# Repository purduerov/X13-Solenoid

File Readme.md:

# Readme for X13-Solenoid

Whenever you make a new part, download the datasheet and save it here _**and**_ with the part in the parts library

Always pull other people's changes before beginning to work
`git pull`

Be sure to push your changes after  working on them. Run:
1. `git add .` to add any files in this directory or a subdirectory
or `git add -u` to add any modified files
2. (Optional) `git clean -nX` to see what ignored files can be removed
	`git clean -fX` removes ignored files (Eagle backups)
3. `git commit -m "helpful commit message"` with a description of the work that you did
4. `git push` to push your work to github

Other helpful commands
* `git status` says information about modified and staged files
* `git log` shows the recent commits of the repository
* `git log filename.extension` show the recent commits for just that file
* `git checkout first-couple-letter-of-commit-id` lets you go back to a previous version
* `git checkout master` brings you back to the latest commit
* `git tag` lists the tags
* `git tag -a orderX -m "the version of the board placed for the X'th order"` tag a specific commit
* `git push --tags` needed to push tags to remote
* `git show orderX` show the commit log for the given tag
* `git checkout orderX` go back and interact with the files at the tagged commit

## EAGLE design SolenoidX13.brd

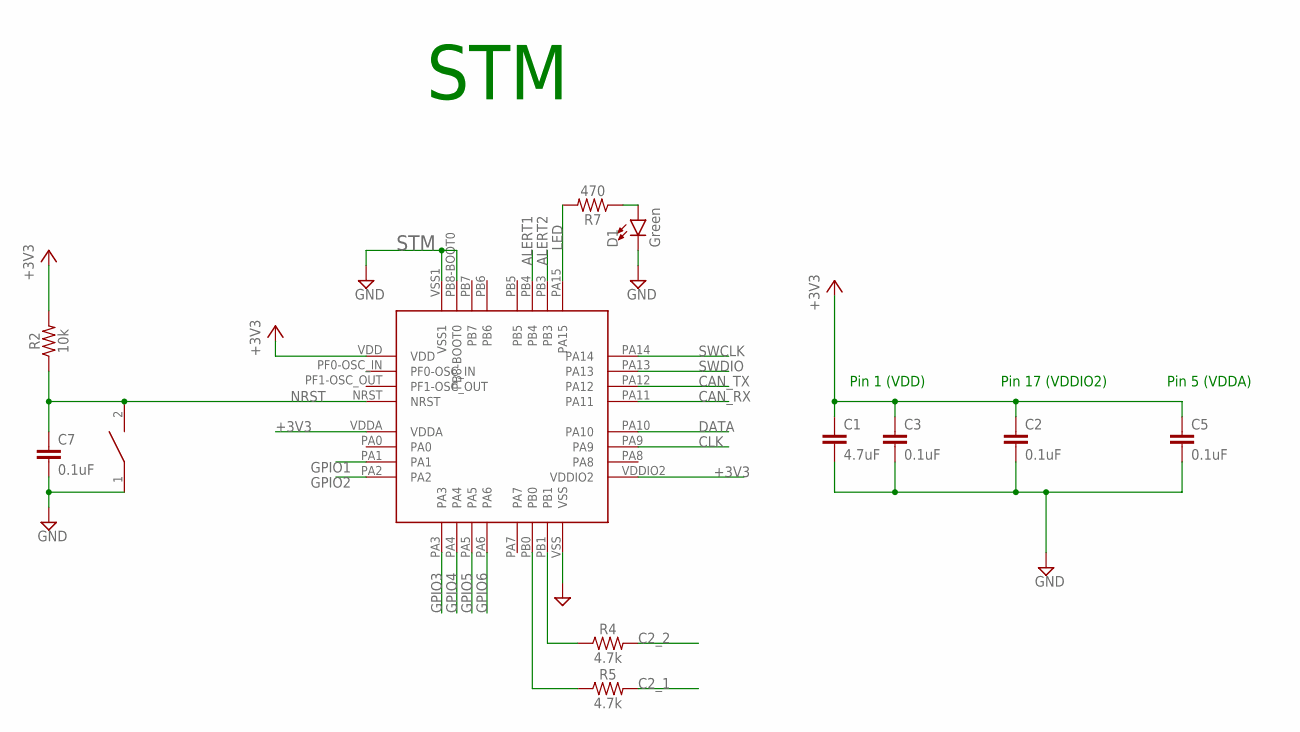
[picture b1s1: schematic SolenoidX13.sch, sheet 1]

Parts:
C1: 4.7uF; 0603
C2, C3, C5, C7: 0.1uF; 0603
D1: Green; LED-0603
R2: 10k; 0603
R4, R5: 4.7k; 0603
R7: 470; 0603
RESET: DISCRETECOMPONENTS_SWITCH; DISCRETECOMPONENTS_SW_2512
STM: STM32F042K6T6

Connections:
+3V3: C1.1, C2.1, C3.1, C5.1, R2.2, STM.VDD, STM.VDDA, STM.VDDIO2; also elsewhere on the board
ALERT1: STM.PB4; also elsewhere on the board
ALERT2: STM.PB3; also elsewhere on the board
C2_1: R5.2; also elsewhere on the board
C2_2: R4.2; also elsewhere on the board
CAN_RX: STM.PA11; also elsewhere on the board
CAN_TX: STM.PA12; also elsewhere on the board
CLK: STM.PA9; also elsewhere on the board
DATA: STM.PA10; also elsewhere on the board
GND: C1.2, C2.2, C3.2, C5.2, C7.2, D1.C, RESET.1, STM.PB8-BOOT0, STM.VSS, STM.VSS1; also elsewhere on the board
GPIO1: STM.PA1; also elsewhere on the board
GPIO2: STM.PA2; also elsewhere on the board
GPIO3: STM.PA3; also elsewhere on the board
GPIO4: STM.PA4; also elsewhere on the board
GPIO5: STM.PA5; also elsewhere on the board
GPIO6: STM.PA6; also elsewhere on the board
LED: R7.2, STM.PA15
unnamed: R4.1, STM.PB1
unnamed: R5.1, STM.PB0
unnamed: D1.A, R7.1
NRST: C7.1, R2.1, RESET.2, STM.NRST; also elsewhere on the board
SWCLK: STM.PA14; also elsewhere on the board
SWDIO: STM.PA13; also elsewhere on the board

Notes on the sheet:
Pin 1 (VDD)
Pin 17 (VDDIO2)
Pin 5 (VDDA)
STM

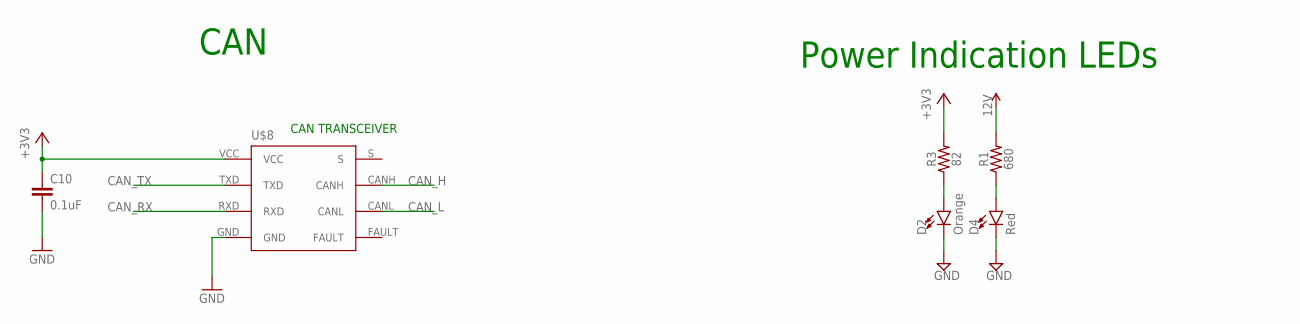
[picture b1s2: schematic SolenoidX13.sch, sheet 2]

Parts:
C10: 0.1uF; 0603
D2: Orange; LED-0603
D4: Red; LED-0603
R1: 680; 0603
R3: 82; 0603
U$8: TCAN337D

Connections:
12V: R1.2; also elsewhere on the board
+3V3: C10.1, R3.2, U$8.VCC; also elsewhere on the board
CAN_H: U$8.CANH; also elsewhere on the board
CAN_L: U$8.CANL; also elsewhere on the board
CAN_RX: U$8.RXD; also elsewhere on the board
CAN_TX: U$8.TXD; also elsewhere on the board
GND: C10.2, D2.C, D4.C, U$8.GND; also elsewhere on the board
unnamed: D4.A, R1.1
unnamed: D2.A, R3.1

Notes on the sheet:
Power Indication LEDs
CAN
CAN TRANSCEIVER

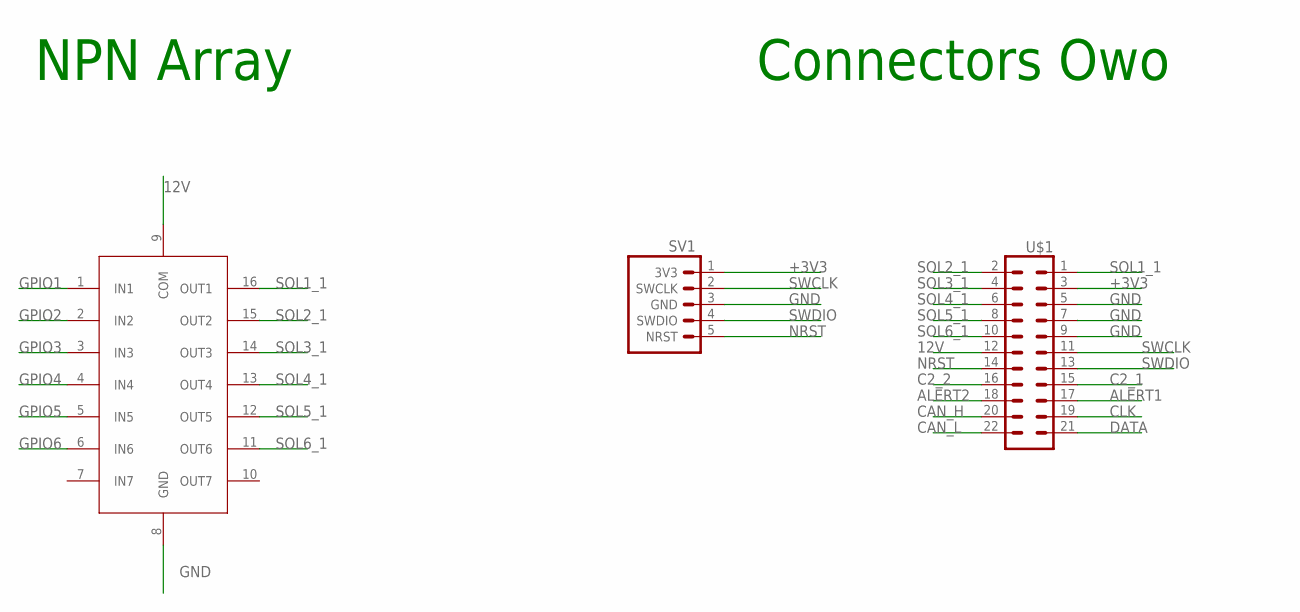
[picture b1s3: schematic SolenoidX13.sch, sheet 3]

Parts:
SV1: 3V3 -SWCLK-GND-SWDIO- NRST; 1X05
U1: ULN2003V12
U$1: SOL-TO-BKP; MMS-111-01-DV

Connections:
12V: U1.9 (COM), U$1.12; also elsewhere on the board
+3V3: SV1.1 (3V3), U$1.3; also elsewhere on the board
ALERT1: U$1.17; also elsewhere on the board
ALERT2: U$1.18; also elsewhere on the board
C2_1: U$1.15; also elsewhere on the board
C2_2: U$1.16; also elsewhere on the board
CAN_H: U$1.20; also elsewhere on the board
CAN_L: U$1.22; also elsewhere on the board
CLK: U$1.19; also elsewhere on the board
DATA: U$1.21; also elsewhere on the board
GND: SV1.3 (GND), U1.8 (GND), U$1.5, U$1.7, U$1.9; also elsewhere on the board
GPIO1: U1.1 (IN1); also elsewhere on the board
GPIO2: U1.2 (IN2); also elsewhere on the board
GPIO3: U1.3 (IN3); also elsewhere on the board
GPIO4: U1.4 (IN4); also elsewhere on the board
GPIO5: U1.5 (IN5); also elsewhere on the board
GPIO6: U1.6 (IN6); also elsewhere on the board
NRST: SV1.5 (NRST), U$1.14; also elsewhere on the board
SOL1_1: U1.16 (OUT1), U$1.1
SOL2_1: U1.15 (OUT2), U$1.2
SOL3_1: U1.14 (OUT3), U$1.4
SOL4_1: U1.13 (OUT4), U$1.6
SOL5_1: U1.12 (OUT5), U$1.8
SOL6_1: U1.11 (OUT6), U$1.10
SWCLK: SV1.2 (SWCLK), U$1.11; also elsewhere on the board
SWDIO: SV1.4 (SWDIO), U$1.13; also elsewhere on the board

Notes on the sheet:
NPN Array
Connectors Owo

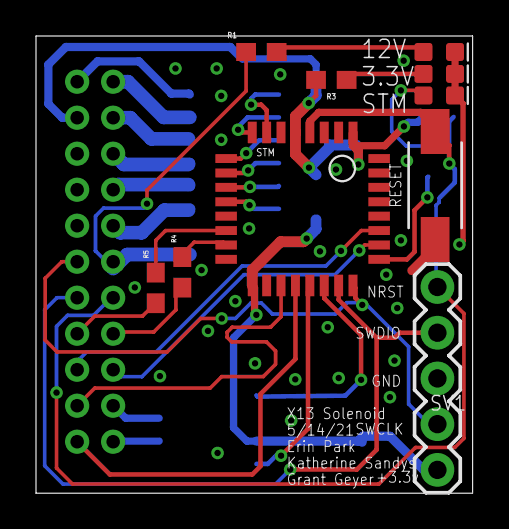
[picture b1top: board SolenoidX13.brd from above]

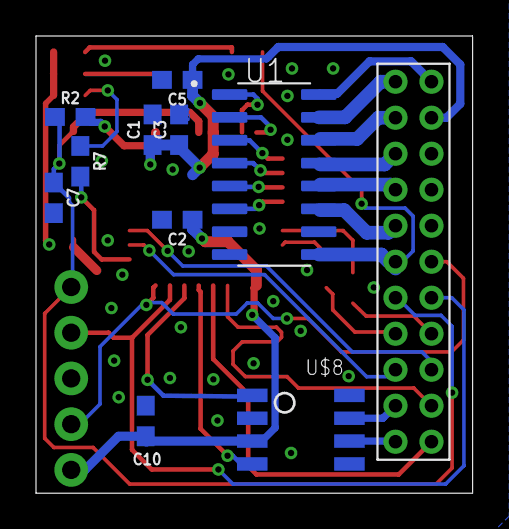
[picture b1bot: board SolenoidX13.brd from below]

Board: 2 copper layers, 24.3 x 25.4 mm, 21 parts (10 on the bottom side), 34 nets.

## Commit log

2020-11-12 First commit with setup
2020-12-03 owo?
2020-12-03 board is done lol
2020-12-03 it is smol now, cap gulag is gone, reset switch updated, clt part added to parts lib
2020-12-04 ready for design review tbh
2020-12-05 okie
2020-12-06 final
2021-01-01 Pretty much ready for production (owo)
2021-01-05 Added nrst pin to connector and routed
2021-01-05 smol changes
2021-01-07 added an OWO
2021-01-09 ground plane? more like ground pain
2021-01-09 grant stuff owo
2021-01-10 Exports prior to ordering
2021-01-20 Fix misprint in schematic
2021-03-13 fixed things
2021-05-15 big pog uwu
2021-05-24 New SWD programming connecotr
2021-10-07 wack
2021-12-31 copied over solenoid
2022-01-05 Revert "copied over solenoid"
    This reverts commit b980a6c83b2fe2ec459018865b78eda5cbb8224a.

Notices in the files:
parts and their libraries:
SparkFun-LED: Licensing: Creative Commons ShareAlike 4.0 International - https://creativecommons.org/licenses/by-sa/4.0
